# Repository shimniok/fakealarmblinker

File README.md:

A fake car alarm blinker circuit based on the venerable 555 timer in astable mode.

In the schematic I set up a frequency and duty cycle that I personally prefer
(around 1-2Hz, 80% OFF / 20% ON duty cycle (555 is sinking current from LED)
but you can easily change the R1/R2/C1 values using various 555 timer calculators
like [this one](http://www.ohmslawcalculator.com/555-astable-calculator)

The project is designed to fit into a Hammond 1555Q box [[pdf](http://www.hammondmfg.com/pdf/1551PFL.pdf)] which is a small flanged-mount box, so it'll be easy to install into your vehicle.

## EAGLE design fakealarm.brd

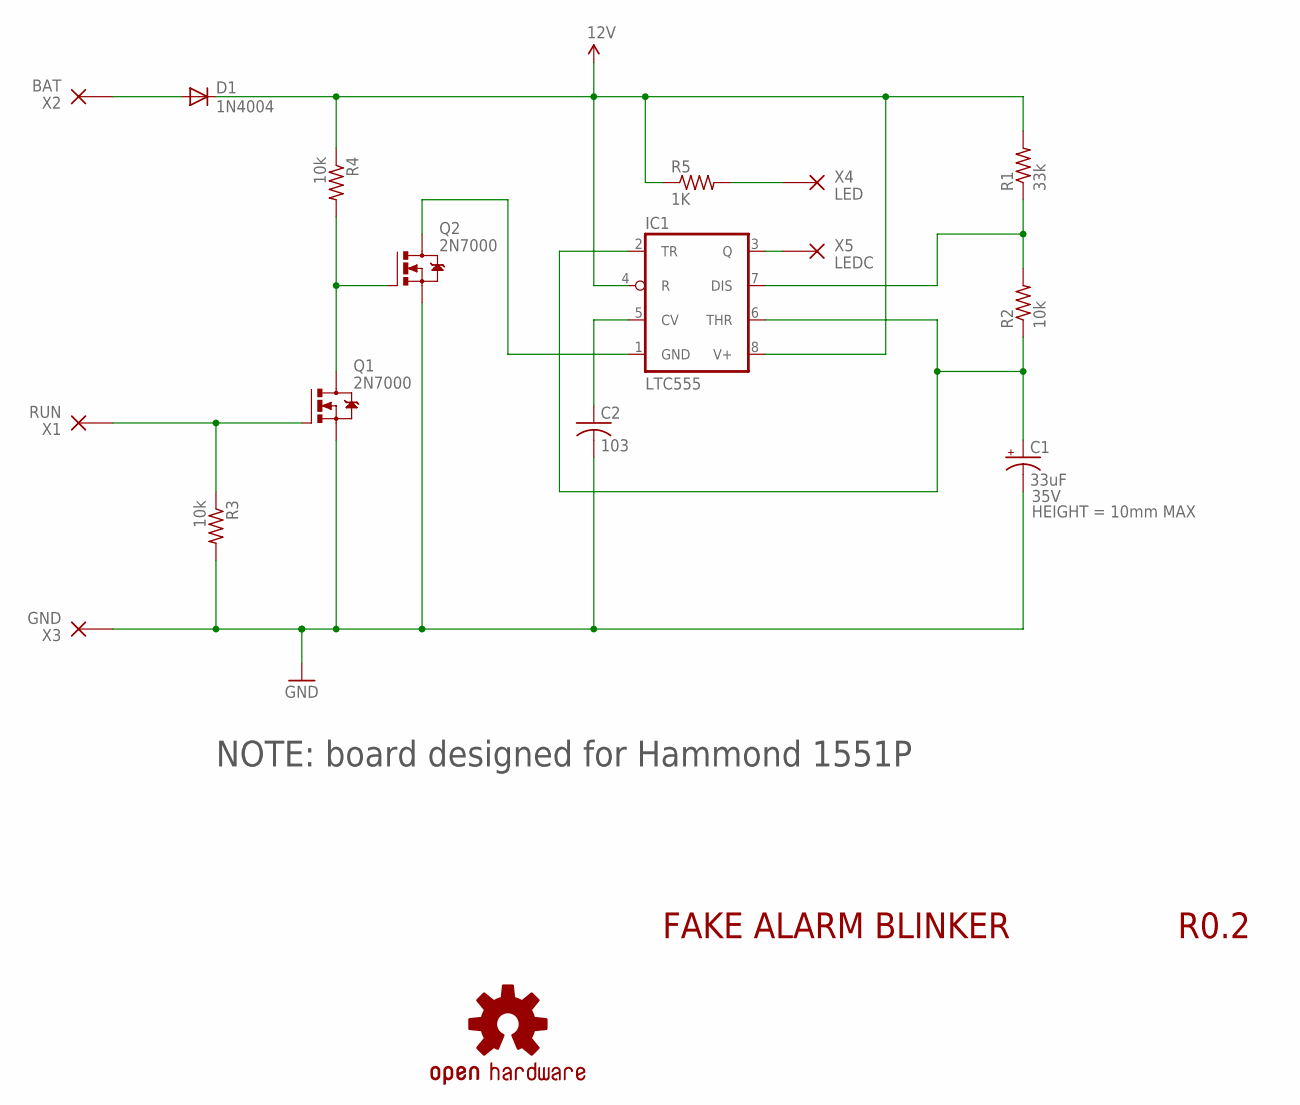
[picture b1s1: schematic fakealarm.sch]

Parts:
C1: 33uF; E2,5-6; VOLTAGE 35V
C2: 103; C050-024X044
D1: 1N4004; DO41-10
IC1: LTC555; DIL08
LOGO1: OSHW-LOGOM; OSHW-LOGO-M
Q1, Q2: 2N7000; TO92D-
R1: 33k; 0207/10
R2, R3, R4: 10k; 0207/10
R5: 1K; 0207/10
X1: RUN; PAD_14GA
X2: BAT; PAD_14GA
X3: GND; PAD_14GA
X4: LED; PAD_24GA
X5: LEDC; PAD_24GA

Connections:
12V: D1.C, IC1.4 (R), IC1.8 (V+), R1.2, R4.1, R5.1
GND: C1.-, C2.2, Q1.1 (S), Q2.1 (S), R3.2, X3.P$1
unnamed: Q1.3 (D), Q2.2 (G), R4.2
unnamed: Q1.2 (G), R3.1, X1.P$1
unnamed: IC1.7 (DIS), R1.1, R2.2
unnamed: C1.+, IC1.2 (TR), IC1.6 (THR), R2.1
unnamed: IC1.1 (GND), Q2.3 (D)
unnamed: D1.A, X2.P$1
unnamed: C2.1, IC1.5 (CV)
unnamed: R5.2, X4.P$1
unnamed: IC1.3 (Q), X5.P$1

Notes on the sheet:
FAKE ALARM BLINKER
R0.2
NOTE: board designed for Hammond 1551P

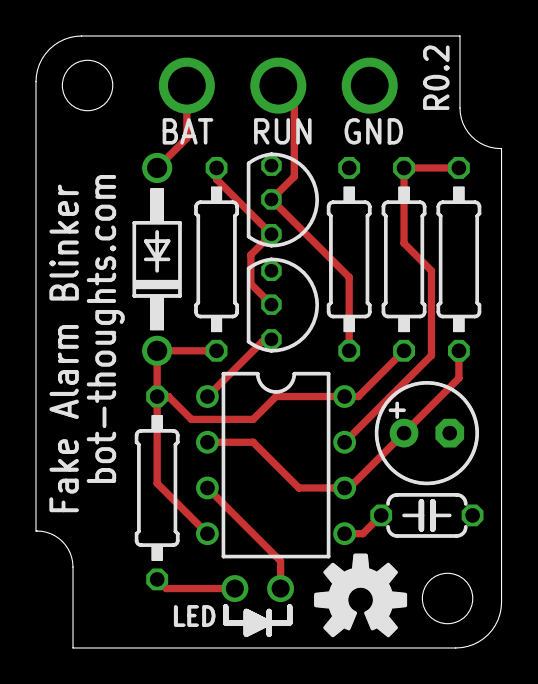
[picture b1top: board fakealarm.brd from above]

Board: 2 copper layers, 25.9 x 34.0 mm, 17 parts (0 on the bottom side), 11 nets.

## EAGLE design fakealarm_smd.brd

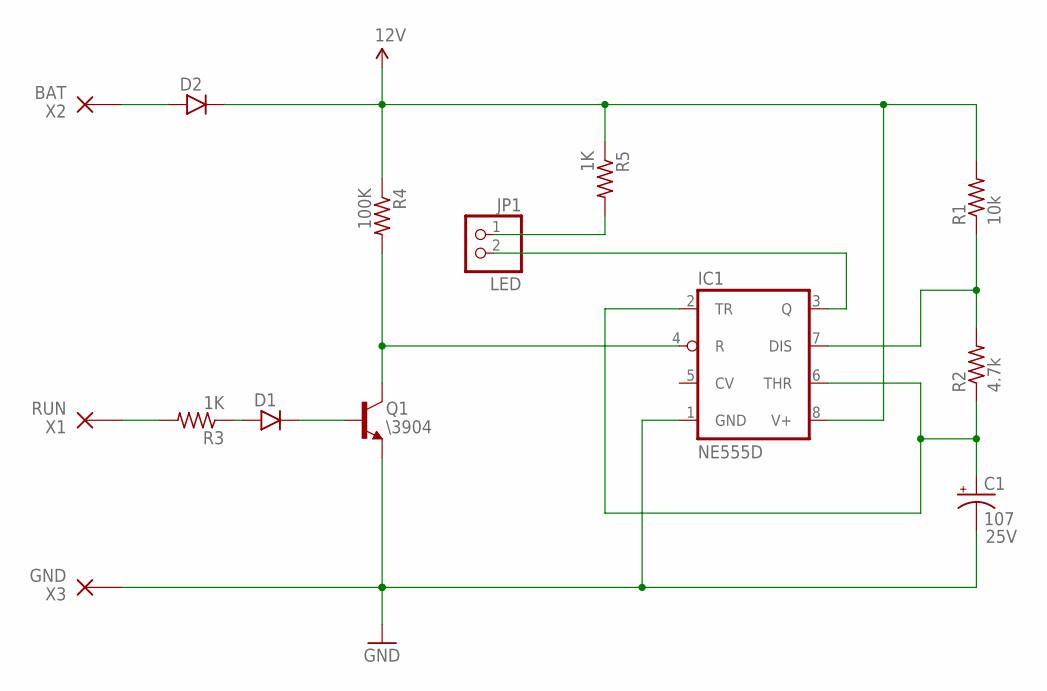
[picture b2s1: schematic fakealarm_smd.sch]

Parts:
C1: 107; PANASONIC_C; VOLTAGE 25V
D1, D2: DIODE_SOD123FL; SOD123FL
IC1: NE555D; SO08
JP1: LED; 1X02-S
Q1: \3904; SOT-23
R1: 10k; R0603
R2: 4.7k; R0603
R3, R5: 1K; R0603
R4: 100K; R0603
X1: RUN; PAD_14GA
X2: BAT; PAD_14GA
X3: GND; PAD_14GA

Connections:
12V: D2.C, IC1.8 (V+), R1.2, R4.1, R5.1
GND: C1.-, IC1.1 (GND), Q1.2 (E), X3.P$1
unnamed: D1.A, R3.1
unnamed: D1.C, Q1.3 (B)
unnamed: IC1.7 (DIS), R1.1, R2.2
unnamed: C1.+, IC1.2 (TR), IC1.6 (THR), R2.1
unnamed: R3.2, X1.P$1
unnamed: D2.A, X2.P$1
unnamed: JP1.1, R5.2
unnamed: IC1.3 (Q), JP1.2
unnamed: IC1.4 (R), Q1.1 (C), R4.2

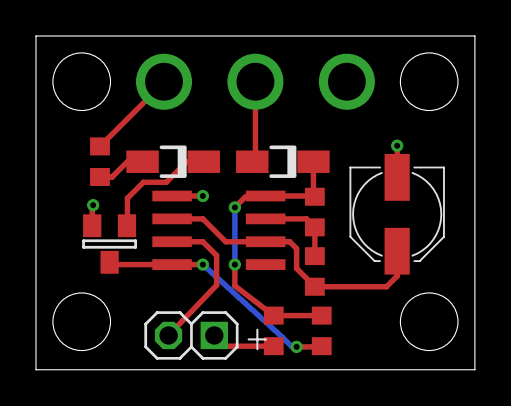
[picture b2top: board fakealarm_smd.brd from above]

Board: 2 copper layers, 24.4 x 18.5 mm, 14 parts (0 on the bottom side), 11 nets.

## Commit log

2015-06-08 added .gitignore
2015-06-08 Added 10nF (0.01uF) bypass on CV, shrank board, moved components around a little
2015-06-08 added oshw logo, minor silk layout tweaks
2015-06-08 Generated silk, added enclosure info to schematic
2015-06-08 Changed Documentation layer visibility to show enclosure info
2015-06-08 updated gitignore with silk file
2015-06-08 fixed drill size for 2nd hole
2015-06-08 redesigned for hammond 1551P (taller enclosure), respec'ed 33uF cap height and voltage, added documentation for max board height' '
2015-06-08 added gerbers
2015-06-08 added zip
2015-06-08 replaced NPN with N-channel MOSFET tied to power, replaced 100k rst with 10k
2015-06-09 Revised switch to use two mosfets to switch entire 555, revised layout, silk, added enclosure info to board
2015-06-09 Layout tweaks on board and schematic. Added reverse protection diode
2015-06-10 generated silk
2015-06-10 revised q2 layout
2015-06-15 Updated gerbers
2015-06-15 updated zip

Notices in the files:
parts and their libraries:
SparkFun-Aesthetics: Licensing: Creative Commons ShareAlike 4.0 International - https://creativecommons.org/licenses/by-sa/4.0
